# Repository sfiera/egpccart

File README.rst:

Game Pocket Computer Cartridges
===============================

* `Simple EEPROM cartridge <rom/>`_
* `3D-printable shell <stl/>`_

License
-------

This work is licensed under `CC-BY 4.0 <LICENSE.txt>`_.

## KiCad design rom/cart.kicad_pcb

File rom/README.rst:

Simple EEPROM cartridge
=======================

.. image:: pcb.png
   :alt: ROM Cartridge PCB
   :width: 300
   :align: center

This is a KiCad_ project for a simple ROM-based cartridge. With a ROM chip soldered directly to the board, it is a drop-in replacement for authentic gamepock cartridges. With a DIP-28 socket, it won’t fit into the original cartridge shell, but can use the cartridge-window.stl bottom instead.

.. _KiCad: https://www.kicad.org/

Materials
---------

* 1 PCB, ENIG or gold-plated (not HASL)
* 1 DIP-28 socket (optional)
* 1 DIP-28 AT28C64 or AT28C256 EEPROM, or compatible
* 1 SOIC-14 74HCT02 quad NOR gate
* 1 0805 0.1uF ceramic capacitor

Jumpers
-------

There are three configurable jumpers which must be set with solder blobs:

* ``A13=LO|AD``
* ``A14=LO|AD``
* ``HI=N|Y``

For basic configurations, resistors R1 and R2 may be left unpopulated. For multi-cart configurations, they may be needed as pull-ups.

================= === === === === ===
Configuration     A13 A14 HI  R1  R2
================= === === === === ===
8kiB ROM          LO  LO  N   DNP DNP
16kiB ROM         AD  LO  N   DNP DNP
32kiB ROM         AD  AD  Y   DNP DNP
4x8kiB multi-ROM  SW  SW  N   10k 10k
2x16kiB multi-ROM AD  SW  N   10k DNP
================= === === === === ===

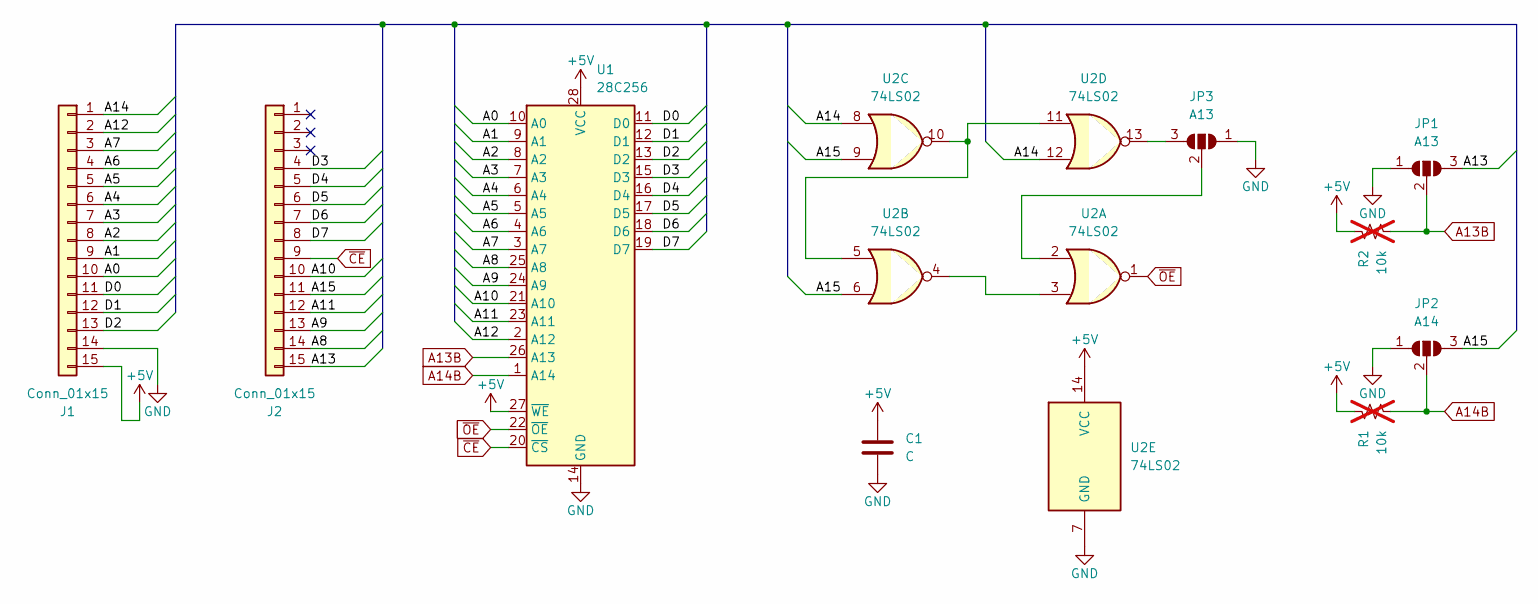
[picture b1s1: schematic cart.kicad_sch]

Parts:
C1: C; C_0805_2012Metric
J1, J2: Conn_01x15; Edge_GamePock
JP1, JP3: A13; SolderJumper-3_P1.3mm_Open_RoundedPad1.0x1.5mm
JP2: A14; SolderJumper-3_P1.3mm_Open_RoundedPad1.0x1.5mm
R1, R2: 10k; R_0805_2012Metric; not fitted
U1: 28C256; DIP-28_W15.24mm
U2: 74LS02; SO-14_3.9x8.65mm_P1.27mm

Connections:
+5V: C1.1, J1.15, R1.1, R2.1, U1.27 (~WE), U1.28 (VCC), U2.14 (VCC)
/A0: J1.10, U1.10 (A0)
/A1: J1.9, U1.9 (A1)
/A2: J1.8, U1.8 (A2)
/A3: J1.7, U1.7 (A3)
/A4: J1.6, U1.6 (A4)
/A5: J1.5, U1.5 (A5)
/A6: J1.4, U1.4 (A6)
/A7: J1.3, U1.3 (A7)
/A8: J2.14, U1.25 (A8)
/A9: J2.13, U1.24 (A9)
/A10: J2.10, U1.21 (A10)
/A11: J2.12, U1.23 (A11)
/A12: J1.2, U1.2 (A12)
/A13: J2.15, JP1.3 (B)
/A14: J1.1, U2.8, U2.12
/A15: J2.11, JP2.3 (B), U2.6, U2.9
/D0: J1.11, U1.11 (D0)
/D1: J1.12, U1.12 (D1)
/D2: J1.13, U1.13 (D2)
/D3: J2.4, U1.15 (D3)
/D4: J2.5, U1.16 (D4)
/D5: J2.6, U1.17 (D5)
/D6: J2.7, U1.18 (D6)
/D7: J2.8, U1.19 (D7)
A13B: JP1.2 (C), R2.2, U1.26 (A13)
A14B: JP2.2 (C), R1.2, U1.1 (A14)
GND: C1.2, J1.14, JP1.1 (A), JP2.1 (A), JP3.1 (A), U1.14 (GND), U2.7 (GND)
unnamed: JP3.3 (B), U2.13
unnamed: JP3.2 (C), U2.2
unnamed: U2.3, U2.4
unnamed: U2.5, U2.10, U2.11
~CE: J2.9, U1.20 (~CS)
~OE: U1.22 (~OE), U2.1

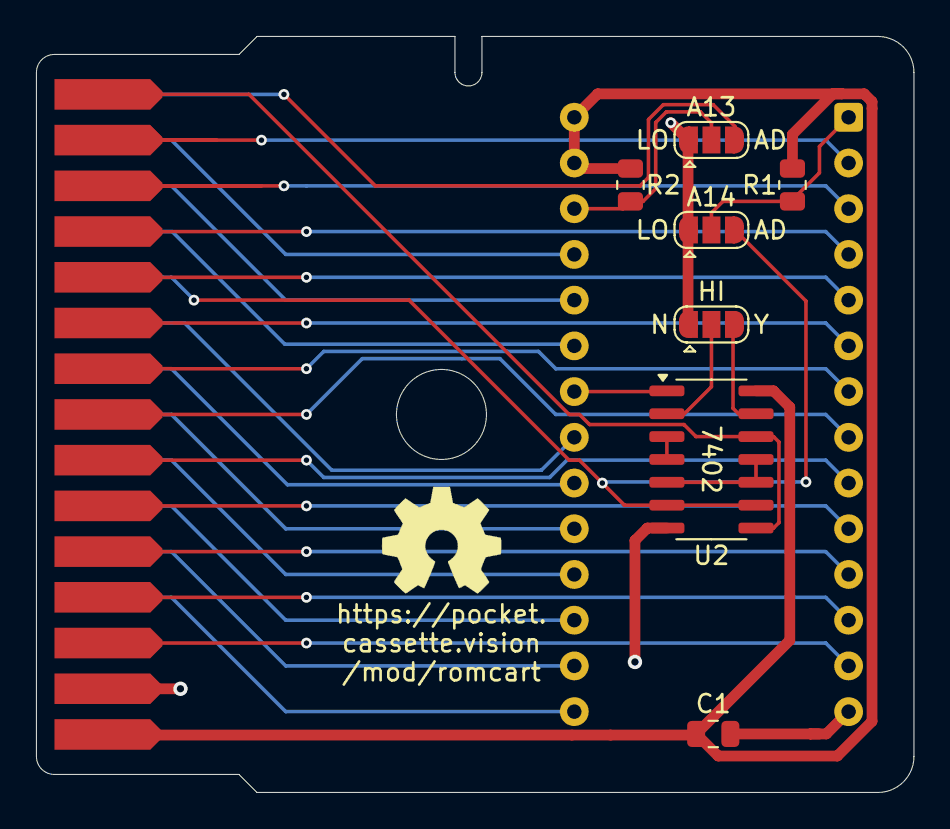
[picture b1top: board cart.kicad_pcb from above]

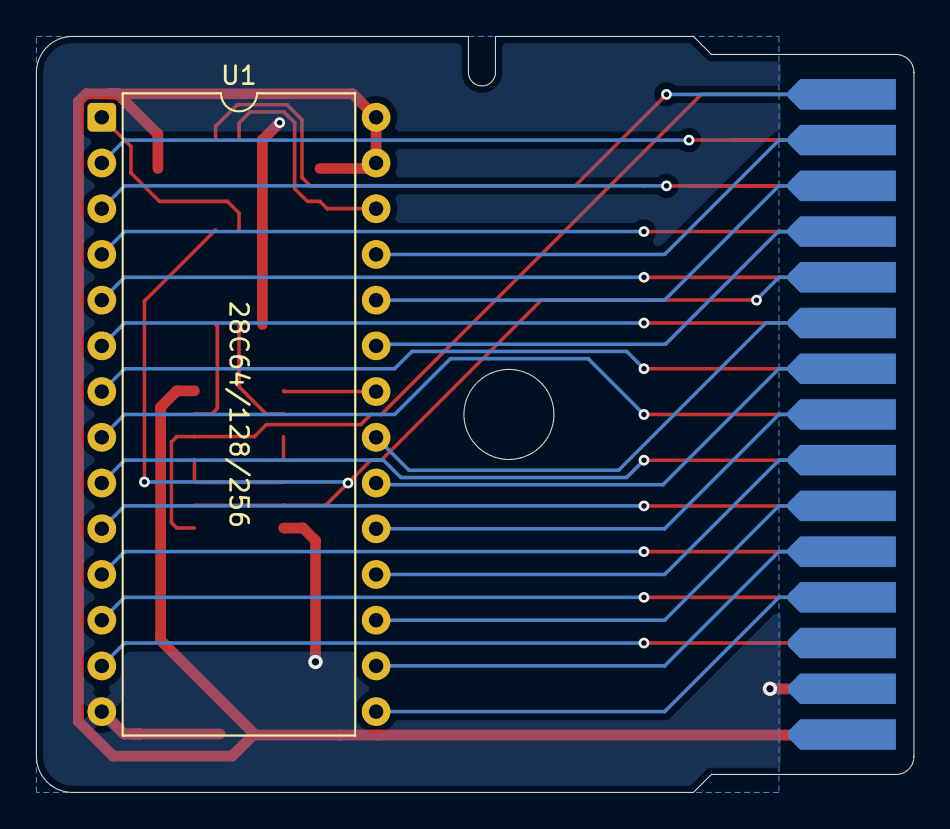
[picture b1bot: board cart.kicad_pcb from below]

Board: 2 copper layers, 48.8 x 42.0 mm, 10 parts (2 on the bottom side), 34 nets.
